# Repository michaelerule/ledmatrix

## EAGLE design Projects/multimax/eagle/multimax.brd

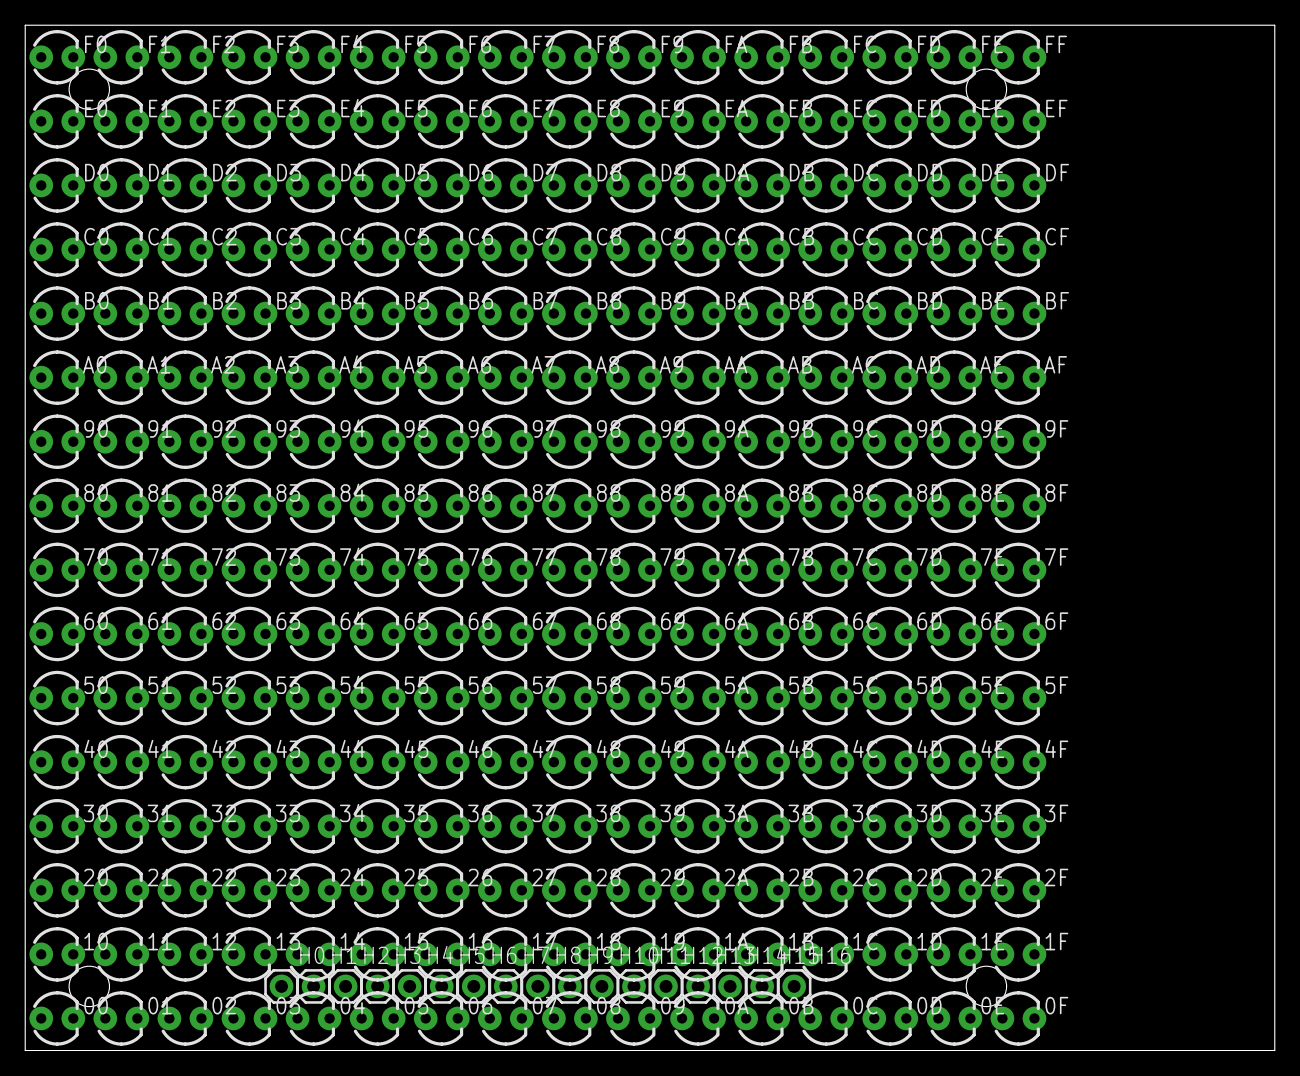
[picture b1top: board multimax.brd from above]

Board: 2 copper layers, 99.1 x 81.3 mm, 273 parts (0 on the bottom side), 17 nets, no tracks yet.

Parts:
00, 0A, 0B, 0C, 0D, 0E, 0F, 01, 1A, 1B, 1C, 1D, 1E, 1F, 02, 2A, 2B, 2C, 2D, 2E, 2F, 03, 3A, 3B, 3C, 3D, 3E, 3F, 04, 4A, 4B, 4C, 4D, 4E, 4F, 05, 5A, 5B, 5C, 5D, 5E, 5F, 06, 6A, 6B, 6C, 6D, 6E, 6F, 07, 7A, 7B, 7C, 7D, 7E, 7F, 08, 8A, 8B, 8C, 8D, 8E, 8F, 09, 9A, 9B, 9C, 9D, 9E, 9F, 10, 11, 12, 13, 14, 15, 16, 17, 18, 19, 20, 21, 22, 23, 24, 25, 26, 27, 28, 29, 30, 31, 32, 33, 34, 35, 36, 37, 38, 39, 40, 41, 42, 43, 44, 45, 46, 47, 48, 49, 50, 51, 52, 53, 54, 55, 56, 57, 58, 59, 60, 61, 62, 63, 64, 65, 66, 67, 68, 69, 70, 71, 72, 73, 74, 75, 76, 77, 78, 79, 80, 81, 82, 83, 84, 85, 86, 87, 88, 89, 90, 91, 92, 93, 94, 95, 96, 97, 98, 99: LED3MM
A0, A1, A2, A3, A4, A5, A6, A7, A8, A9: LED3MM
AA: LED3MM
AB: LED3MM
AC: LED3MM
AD: LED3MM
AE: LED3MM
AF: LED3MM
B0, B1, B2, B3, B4, B5, B6, B7, B8, B9: LED3MM
BA: LED3MM
BB: LED3MM
BC: LED3MM
BD: LED3MM
BE: LED3MM
BF: LED3MM
C0, C1, C2, C3, C4, C5, C6, C7, C8, C9: LED3MM
CA: LED3MM
CB: LED3MM
CC: LED3MM
CD: LED3MM
CE: LED3MM
CF: LED3MM
D0, D1, D2, D3, D4, D5, D6, D7, D8, D9: LED3MM
DA: LED3MM
DB: LED3MM
DC: LED3MM
DD: LED3MM
DE: LED3MM
DF: LED3MM
E0, E1, E2, E3, E4, E5, E6, E7, E8, E9: LED3MM
EA: LED3MM
EB: LED3MM
EC: LED3MM
ED: LED3MM
EE: LED3MM
EF: LED3MM
F0, F1, F2, F3, F4, F5, F6, F7, F8, F9: LED3MM
FA: LED3MM
FB: LED3MM
FC: LED3MM
FD: LED3MM
FE: LED3MM
FF: LED3MM
H0, H1, H2, H3, H4, H5, H6, H7, H8, H9, H10, H11, H12, H13, H14, H15, H16: 1X01

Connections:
D: 00.A, 11.A, 22.A, 33.A, 44.A, 55.A, 66.A, 77.A, 88.A, 99.A, AA.A, BB.A, CC.A, DD.A, EE.A, FF.A, H16.1
S0: 00.K, 0A.A, 0B.A, 0C.A, 0D.A, 0E.A, 0F.A, 01.A, 02.A, 03.A, 04.A, 05.A, 06.A, 07.A, 08.A, 09.A, 10.K, 20.K, 30.K, 40.K, 50.K, 60.K, 70.K, 80.K, 90.K, A0.K, B0.K, C0.K, D0.K, E0.K, F0.K, H0.1
S1: 01.K, 1A.A, 1B.A, 1C.A, 1D.A, 1E.A, 1F.A, 10.A, 11.K, 12.A, 13.A, 14.A, 15.A, 16.A, 17.A, 18.A, 19.A, 21.K, 31.K, 41.K, 51.K, 61.K, 71.K, 81.K, 91.K, A1.K, B1.K, C1.K, D1.K, E1.K, F1.K, H1.1
S2: 02.K, 2A.A, 2B.A, 2C.A, 2D.A, 2E.A, 2F.A, 12.K, 20.A, 21.A, 22.K, 23.A, 24.A, 25.A, 26.A, 27.A, 28.A, 29.A, 32.K, 42.K, 52.K, 62.K, 72.K, 82.K, 92.K, A2.K, B2.K, C2.K, D2.K, E2.K, F2.K, H2.1
S3: 03.K, 3A.A, 3B.A, 3C.A, 3D.A, 3E.A, 3F.A, 13.K, 23.K, 30.A, 31.A, 32.A, 33.K, 34.A, 35.A, 36.A, 37.A, 38.A, 39.A, 43.K, 53.K, 63.K, 73.K, 83.K, 93.K, A3.K, B3.K, C3.K, D3.K, E3.K, F3.K, H3.1
S4: 04.K, 4A.A, 4B.A, 4C.A, 4D.A, 4E.A, 4F.A, 14.K, 24.K, 34.K, 40.A, 41.A, 42.A, 43.A, 44.K, 45.A, 46.A, 47.A, 48.A, 49.A, 54.K, 64.K, 74.K, 84.K, 94.K, A4.K, B4.K, C4.K, D4.K, E4.K, F4.K, H4.1
S5: 05.K, 5A.A, 5B.A, 5C.A, 5D.A, 5E.A, 5F.A, 15.K, 25.K, 35.K, 45.K, 50.A, 51.A, 52.A, 53.A, 54.A, 55.K, 56.A, 57.A, 58.A, 59.A, 65.K, 75.K, 85.K, 95.K, A5.K, B5.K, C5.K, D5.K, E5.K, F5.K, H5.1
S6: 06.K, 6A.A, 6B.A, 6C.A, 6D.A, 6E.A, 6F.A, 16.K, 26.K, 36.K, 46.K, 56.K, 60.A, 61.A, 62.A, 63.A, 64.A, 65.A, 66.K, 67.A, 68.A, 69.A, 76.K, 86.K, 96.K, A6.K, B6.K, C6.K, D6.K, E6.K, F6.K, H6.1
S7: 07.K, 7A.A, 7B.A, 7C.A, 7D.A, 7E.A, 7F.A, 17.K, 27.K, 37.K, 47.K, 57.K, 67.K, 70.A, 71.A, 72.A, 73.A, 74.A, 75.A, 76.A, 77.K, 78.A, 79.A, 87.K, 97.K, A7.K, B7.K, C7.K, D7.K, E7.K, F7.K, H7.1
S8: 08.K, 8A.A, 8B.A, 8C.A, 8D.A, 8E.A, 8F.A, 18.K, 28.K, 38.K, 48.K, 58.K, 68.K, 78.K, 80.A, 81.A, 82.A, 83.A, 84.A, 85.A, 86.A, 87.A, 88.K, 89.A, 98.K, A8.K, B8.K, C8.K, D8.K, E8.K, F8.K, H8.1
S9: 09.K, 9A.A, 9B.A, 9C.A, 9D.A, 9E.A, 9F.A, 19.K, 29.K, 39.K, 49.K, 59.K, 69.K, 79.K, 89.K, 90.A, 91.A, 92.A, 93.A, 94.A, 95.A, 96.A, 97.A, 98.A, 99.K, A9.K, B9.K, C9.K, D9.K, E9.K, F9.K, H9.1
S10: 0A.K, 1A.K, 2A.K, 3A.K, 4A.K, 5A.K, 6A.K, 7A.K, 8A.K, 9A.K, A0.A, A1.A, A2.A, A3.A, A4.A, A5.A, A6.A, A7.A, A8.A, A9.A, AA.K, AB.A, AC.A, AD.A, AE.A, AF.A, BA.K, CA.K, DA.K, EA.K, FA.K, H10.1
S11: 0B.K, 1B.K, 2B.K, 3B.K, 4B.K, 5B.K, 6B.K, 7B.K, 8B.K, 9B.K, AB.K, B0.A, B1.A, B2.A, B3.A, B4.A, B5.A, B6.A, B7.A, B8.A, B9.A, BA.A, BB.K, BC.A, BD.A, BE.A, BF.A, CB.K, DB.K, EB.K, FB.K, H11.1
S12: 0C.K, 1C.K, 2C.K, 3C.K, 4C.K, 5C.K, 6C.K, 7C.K, 8C.K, 9C.K, AC.K, BC.K, C0.A, C1.A, C2.A, C3.A, C4.A, C5.A, C6.A, C7.A, C8.A, C9.A, CA.A, CB.A, CC.K, CD.A, CE.A, CF.A, DC.K, EC.K, FC.K, H12.1
S13: 0D.K, 1D.K, 2D.K, 3D.K, 4D.K, 5D.K, 6D.K, 7D.K, 8D.K, 9D.K, AD.K, BD.K, CD.K, D0.A, D1.A, D2.A, D3.A, D4.A, D5.A, D6.A, D7.A, D8.A, D9.A, DA.A, DB.A, DC.A, DD.K, DE.A, DF.A, ED.K, FD.K, H13.1
S14: 0E.K, 1E.K, 2E.K, 3E.K, 4E.K, 5E.K, 6E.K, 7E.K, 8E.K, 9E.K, AE.K, BE.K, CE.K, DE.K, E0.A, E1.A, E2.A, E3.A, E4.A, E5.A, E6.A, E7.A, E8.A, E9.A, EA.A, EB.A, EC.A, ED.A, EE.K, EF.A, FE.K, H14.1
S15: 0F.K, 1F.K, 2F.K, 3F.K, 4F.K, 5F.K, 6F.K, 7F.K, 8F.K, 9F.K, AF.K, BF.K, CF.K, DF.K, EF.K, F0.A, F1.A, F2.A, F3.A, F4.A, F5.A, F6.A, F7.A, F8.A, F9.A, FA.A, FB.A, FC.A, FD.A, FE.A, FF.K, H15.1

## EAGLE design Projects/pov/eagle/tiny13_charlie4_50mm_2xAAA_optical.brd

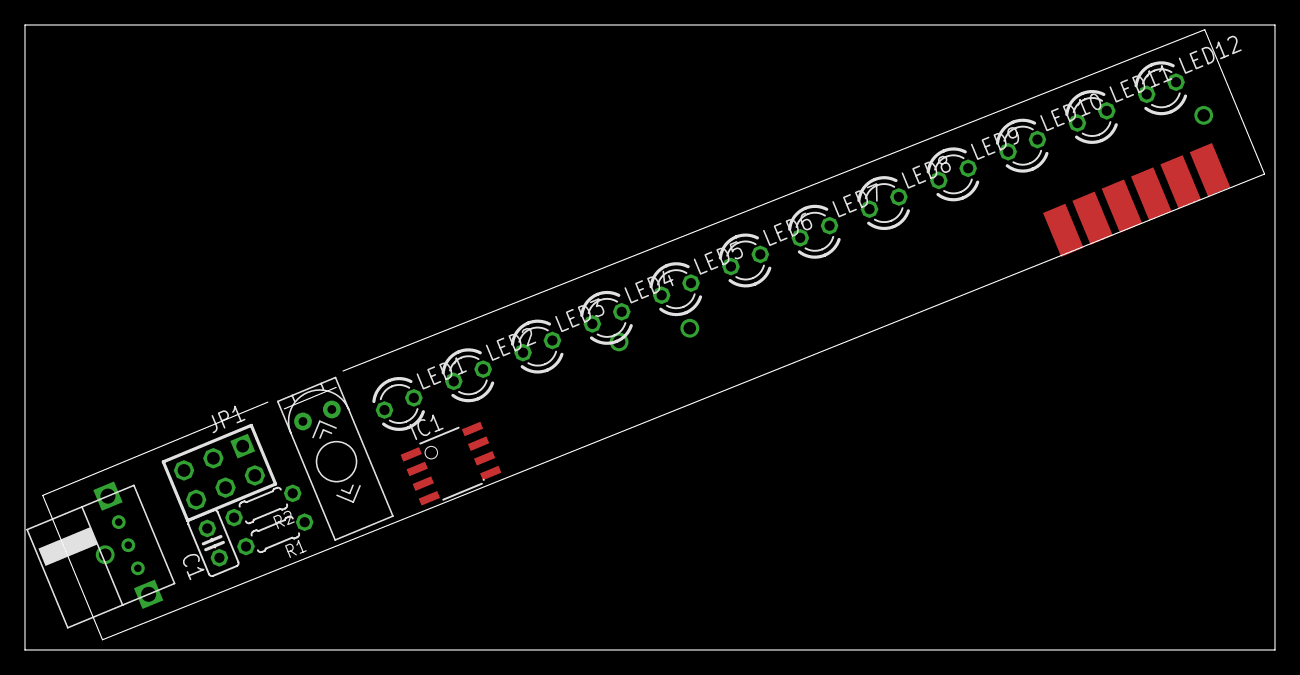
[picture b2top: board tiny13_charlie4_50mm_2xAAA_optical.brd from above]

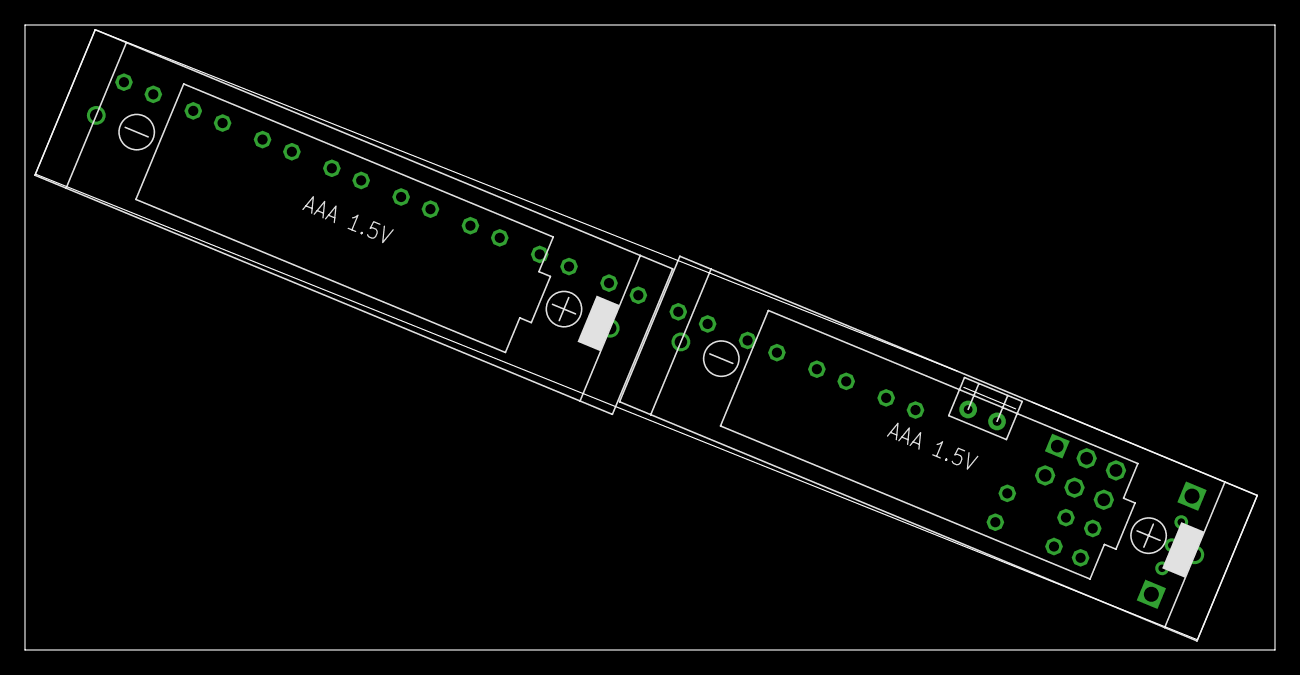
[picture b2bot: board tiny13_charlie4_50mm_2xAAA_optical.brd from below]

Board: 2 copper layers, 100.0 x 50.0 mm, 22 parts (2 on the bottom side), 11 nets, no tracks yet.

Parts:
C1: C025-025X050
IC1: TINY13-20SSU; 8S1
JP1: AVR-ISP-6
LED1, LED2, LED3, LED4, LED5, LED6, LED7, LED8, LED9, LED10, LED11, LED12: LED3MM
R1, R2: 0204/5
U$1: TILT_SWITCH_WRAP; TILT_SWITCH_VAR
U$2: AVR_ISP_6_PIN_1X6_SMT_CONTACT_BIG; CONTACT_ISP_PROGRAMMER_1X6_ATMEL
U$3, U$5: 1XAAA; AAA_THROUGH_HOLE
U$4: SWITCH

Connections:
GND: C1.2, IC1.4, JP1.6, U$1.P$1, U$2.GND, U$4.1
unnamed: IC1.2, LED3.K, LED4.A, LED5.K, LED6.A, LED7.A, LED8.K
unnamed: IC1.7, JP1.3, LED1.K, LED2.A, LED3.A, LED4.K, LED11.A, LED12.K, U$2.SCK
unnamed: R2.1, U$1.P$2
unnamed: IC1.3, LED7.K, LED8.A, LED9.K, LED10.A, LED11.K, LED12.A
unnamed: IC1.5, JP1.4, R2.2, U$2.MOSI
unnamed: IC1.1, JP1.5, R1.2, U$2.RST
unnamed: U$3.P$2, U$5.P$1
unnamed: IC1.6, JP1.1, LED1.A, LED2.K, LED5.A, LED6.K, LED9.A, LED10.K, U$2.MISO
unnamed: U$4.2, U$5.P$2
VCC: C1.1, IC1.8, JP1.2, R1.1, U$2.VCC, U$3.P$1

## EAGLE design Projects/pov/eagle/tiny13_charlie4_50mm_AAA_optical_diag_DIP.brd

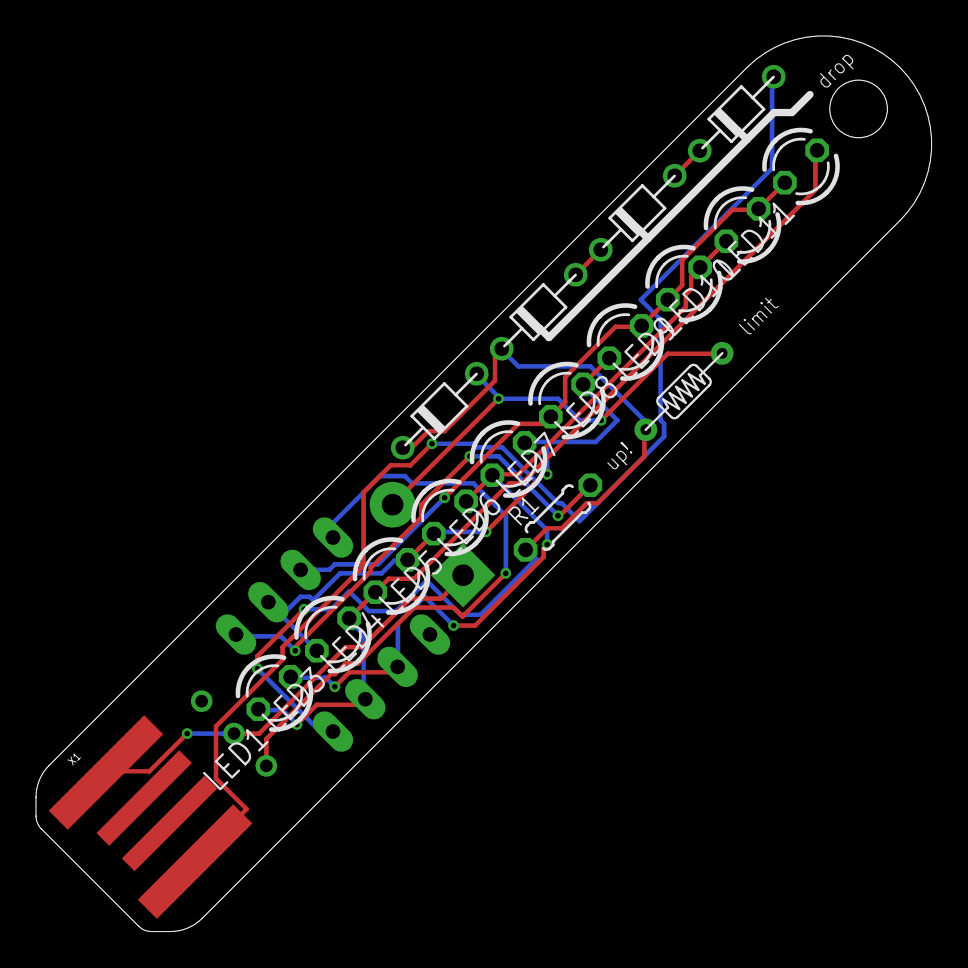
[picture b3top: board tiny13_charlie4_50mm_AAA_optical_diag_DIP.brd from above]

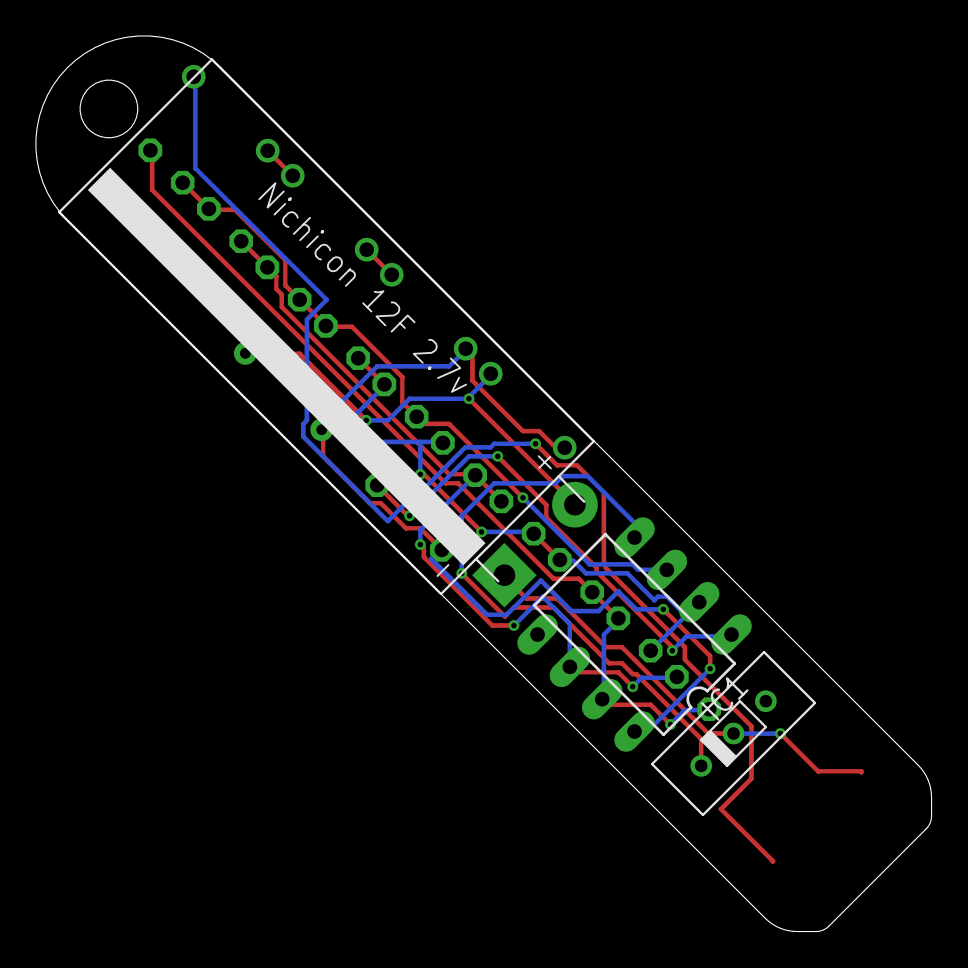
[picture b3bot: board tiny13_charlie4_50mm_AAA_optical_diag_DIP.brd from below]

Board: 2 copper layers, 49.8 x 49.8 mm, 20 parts (3 on the bottom side), 12 nets.

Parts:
IC1: TINY13V-10PU; DIL08
LED1, LED3, LED4, LED5, LED6, LED7, LED8, LED9, LED10, LED11: LED3MM
R1: 0204/5
U$1: R-6
U$2, U$3, U$6, U$7: D-6; D-7.5
U$5: NICHICON_12F; NICHICON_10X30
U$8: SPST_SWITCH_MICRO_PTH; SPSTMICRO
X1: USBPCB; USB-A-PCB

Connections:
GND: IC1.4, U$8.P$1
unnamed: IC1.2, LED3.K, LED4.A, LED5.K, LED6.A, LED7.A, LED8.K
unnamed: IC1.7, LED1.K, LED3.A, LED4.K, LED11.A
unnamed: IC1.3, LED7.K, LED8.A, LED9.K, LED10.A, LED11.K
unnamed: IC1.1, R1.2
unnamed: U$5.P$1, U$8.P$2, X1.GND
unnamed: IC1.6, LED1.A, LED5.A, LED6.K, LED9.A, LED10.K
unnamed: U$1.P$1, U$5.P$2, U$7.A
unnamed: U$2.C, U$3.A
unnamed: U$3.C, U$6.A
unnamed: U$2.A, X1.5V
VCC: IC1.8, R1.1, U$1.P$2, U$6.C, U$7.C

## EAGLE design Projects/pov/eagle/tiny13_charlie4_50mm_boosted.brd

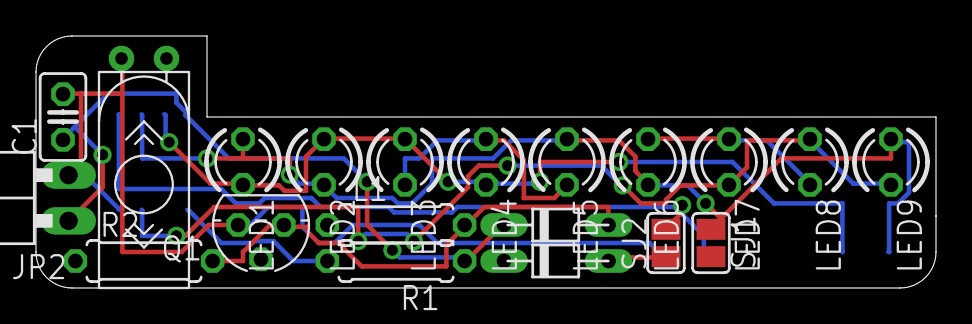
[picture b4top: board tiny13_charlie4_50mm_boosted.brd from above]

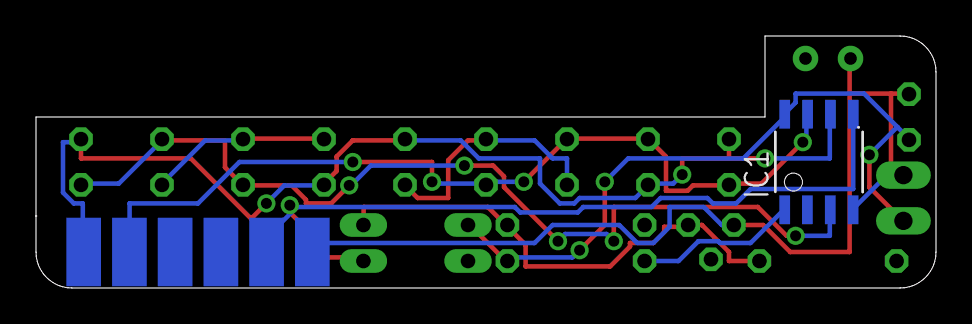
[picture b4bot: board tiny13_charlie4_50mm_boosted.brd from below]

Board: 2 copper layers, 50.0 x 14.0 mm, 22 parts (2 on the bottom side), 12 nets.

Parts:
C1: C025-025X050
IC1: TINY13-20SSU; 8S1
JP2: 1X02/90
L1: 0207/7
LED1, LED2, LED3, LED4, LED5, LED6, LED7, LED8, LED9: LED3MM
Q1: BSS101; TO92
R1, R2: 0207/7
SJ1, SJ2: SJ
U$1: TILT_SWITCH_MECHANICAL
U$2: AVR_ISP_6_PIN_1X6_SMT_CONTACT_PROGRAMMER; CONTACT_ISP_PROGRAMMER_1X6_ATMEL
U$3, U$4: D-6; D-7.5

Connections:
GND: C1.2, IC1.4, JP2.2, Q1.1, U$1.P$1, U$2.GND
unnamed: IC1.2, LED3.K, LED4.A, LED5.K, LED6.A, LED7.A, LED8.K
unnamed: IC1.7, LED1.K, LED2.A, LED3.A, LED4.K, U$2.SCK
unnamed: L1.2, Q1.3, R2.2, U$1.P$2, U$3.A
unnamed: IC1.3, LED7.K, LED8.A, LED9.K
unnamed: R2.1, U$4.C
unnamed: IC1.1, R1.2, U$2.RST
unnamed: IC1.5, SJ2.2, U$2.MOSI
unnamed: IC1.6, LED1.A, LED2.K, LED5.A, LED6.K, LED9.A, SJ1.1, U$2.MISO
unnamed: Q1.2, SJ1.2
unnamed: SJ2.1, U$4.A
VCC: C1.1, IC1.8, JP2.1, R1.1, U$2.VCC, U$3.C

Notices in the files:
parts and their libraries:
SparkFun-Connectors: Licensing: CC v3.0 Share-Alike You are welcome to use this library for commercial purposes.
